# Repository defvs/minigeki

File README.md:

# M.I.N.I.G.E.K.I : a portable ONGEKI controller

A portable implementation of an ONGEKI controller, with all necessary buttons, two macros, RGB LED support, USB-C.

## Hardware setup

- Raspberry RP2040 microcontroller
- 10 hotswappable Cherry MX switches (2x Start, 2x Wall, 2x R+G+B), 2 Macro switches
- 10 RGB daisy-chained WS2812-compatible LEDs (Under every switch except Start, and two under the board)
- USB Type-C connector for both data and power. 

## Software capabilities

- HID Gamepad mode or HID Mouse/Keyboard mode
    - Switchable on boot
- Software addressable RGB via HID
- Auto-rollback to static RGB LEDs if no HID is detected
    - LED can be disabled on boot
- High polling rate
- Switch debouncing
- 8-bit slider position

## Based on / sources

- This project's code is based on SpeedyPotato's [Pico-Game-Controller](https://github.com/speedypotato/Pico-Game-Controller)
    - It also includes sources from Raspberry Pi's [pico-examples](https://github.com/raspberrypi/pico-examples)
- This project's PCB is based on Raspberry Pi's [RP2040-Minimal design](https://datasheets.raspberrypi.com/rp2040/Minimal-KiCAD.zip)

## License and Open Source licensing

minigeki is under GPLv3 in compliance with the usage of existing GPLv3 code. License information can be found in the LICENSE file.

A list of open source components and their licenses can be found in the LICENSING file.

## Extra credit and thank you

- CrazyRedMachine
- megumi_akasaka
- SpeedyPotato

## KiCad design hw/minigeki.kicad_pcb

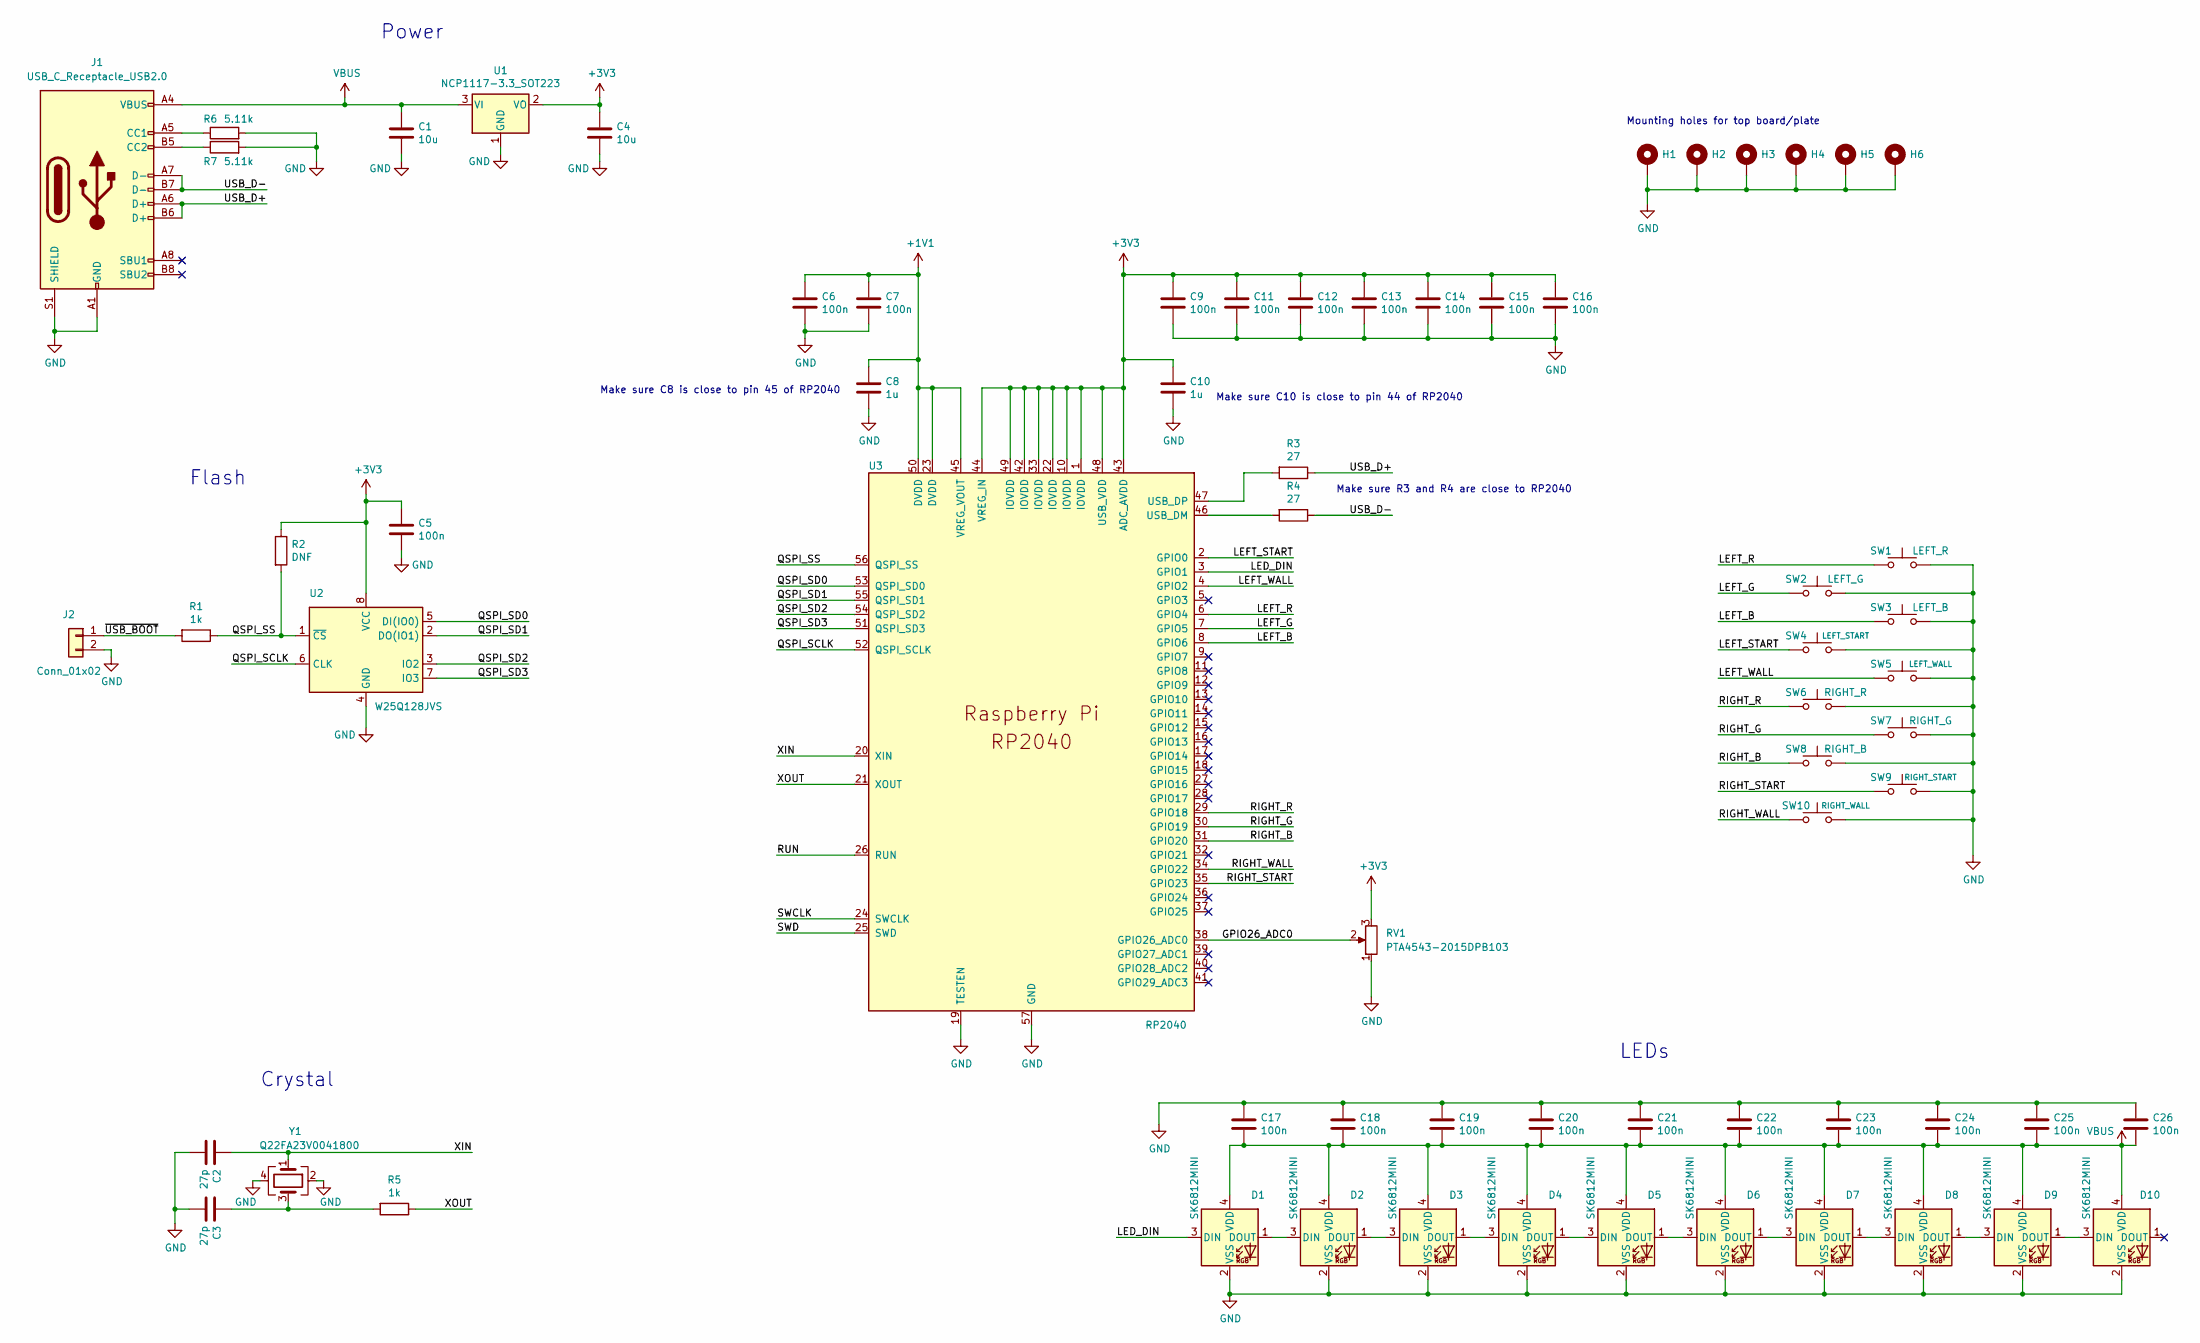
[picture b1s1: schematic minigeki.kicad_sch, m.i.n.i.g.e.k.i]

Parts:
C1, C4: 10u; C_0805_2012Metric
C2, C3: 27p; C_0402_1005Metric
C5, C6, C7, C9, C11, C12, C13, C14, C15, C16, C17, C18, C19, C20, C21, C22, C23, C24, C25, C26: 100n; C_0402_1005Metric
C8, C10: 1u; C_0402_1005Metric
D1, D2, D3, D4, D5, D6, D7, D8, D9, D10: SK6812MINI; LED_SK6812MINI_PLCC4_3.5x3.5mm_P1.75mm; MPN SK6812MINI
H1, H2, H3, H4, H5, H6: MountingHole_Pad; MountingHole_2.2mm_M2_Pad_TopOnly
J1: USB_C_Receptacle_USB2.0; USB_C_Receptacle_XKB_U262-16XN-4BVC11; MPN U262-161N-4BVC11
J2: Conn_01x02; PinHeader_1x02_P2.54mm_Vertical
R1, R5: 1k; C_0402_1005Metric
R2: DNF; C_0402_1005Metric
R3, R4: 27; C_0402_1005Metric
R6, R7: 5.11k; R_0402_1005Metric
RV1: PTA4543-2015DPB103; PTAXX43; MPN PTA4543-2015DPB103
SW1: LEFT_R; SW_Hotswap_Kailh_MX_1.00u
SW2: LEFT_G; SW_Hotswap_Kailh_MX_1.00u
SW3: LEFT_B; SW_Hotswap_Kailh_MX_1.00u
SW4: LEFT_START; SW_Hotswap_Kailh_MX_1.00u
SW5: LEFT_WALL; SW_Hotswap_Kailh_MX_2.00u
SW6: RIGHT_R; SW_Hotswap_Kailh_MX_1.00u
SW7: RIGHT_G; SW_Hotswap_Kailh_MX_1.00u
SW8: RIGHT_B; SW_Hotswap_Kailh_MX_1.00u
SW9: RIGHT_START; SW_Hotswap_Kailh_MX_1.00u
SW10: RIGHT_WALL; SW_Hotswap_Kailh_MX_2.00u
U1: NCP1117-3.3_SOT223; SOT-223-3_TabPin2; MPN NCP1117ST33T3G
U2: W25Q128JVS; SOIC-8_5.23x5.23mm_P1.27mm; MPN W25Q128JVS
U3: RP2040; RP2040-QFN-56; MPN RP2040
Y1: Q22FA23V0041800; Crystal_SMD_3225-4Pin_3.2x2.5mm; MPN Q22FA23V0041800

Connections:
+1V1: C6.1, C7.1, C8.1, U3.23 (DVDD), U3.45 (VREG_VOUT), U3.50 (DVDD)
+3V3: C4.1, C5.1, C9.1, C10.1, C11.1, C12.1, C13.1, C14.1, C15.1, C16.1, R2.1, RV1.3, U1.2 (VO), U2.8 (VCC), U3.1 (IOVDD), U3.10 (IOVDD), U3.22 (IOVDD), U3.33 (IOVDD), U3.42 (IOVDD), U3.43 (ADC_AVDD), U3.44 (VREG_IN), U3.48 (USB_VDD), U3.49 (IOVDD)
/GPIO26_ADC0: RV1.2, U3.38 (GPIO26_ADC0)
/LED_DIN: D1.3 (DIN), U3.3 (GPIO1)
/LEFT_B: SW3.1, U3.8 (GPIO6)
/LEFT_G: SW2.1, U3.7 (GPIO5)
/LEFT_R: SW1.1, U3.6 (GPIO4)
/LEFT_START: SW4.1, U3.2 (GPIO0)
/LEFT_WALL: SW5.1, U3.4 (GPIO2)
/QSPI_SCLK: U2.6 (CLK), U3.52 (QSPI_SCLK)
/QSPI_SD0: U2.5 (DI(IO0)), U3.53 (QSPI_SD0)
/QSPI_SD1: U2.2 (DO(IO1)), U3.55 (QSPI_SD1)
/QSPI_SD2: U2.3 (IO2), U3.54 (QSPI_SD2)
/QSPI_SD3: U2.7 (IO3), U3.51 (QSPI_SD3)
/QSPI_SS: R1.1, R2.2, U2.1 (~CS), U3.56 (QSPI_SS)
/RIGHT_B: SW8.1, U3.31 (GPIO20)
/RIGHT_G: SW7.1, U3.30 (GPIO19)
/RIGHT_R: SW6.1, U3.29 (GPIO18)
/RIGHT_START: SW9.1, U3.35 (GPIO23)
/RIGHT_WALL: SW10.1, U3.34 (GPIO22)
/RUN: U3.26 (RUN)
/SWCLK: U3.24 (SWCLK)
/SWD: U3.25 (SWD)
/USB_D+: J1.A6 (D+), J1.B6 (D+), R3.1
/USB_D-: J1.A7 (D-), J1.B7 (D-), R4.1
/XIN: C2.1, U3.20 (XIN), Y1.1
/XOUT: R5.1, U3.21 (XOUT)
/~USB_BOOT: J2.1, R1.2
GND: C1.2, C2.2, C3.2, C4.2, C5.2, C6.2, C7.2, C8.2, C9.2, C10.2, C11.2, C12.2, C13.2, C14.2, C15.2, C16.2, C17.1, C18.1, C19.1, C20.1, C21.1, C22.1, C23.1, C24.1, C25.1, C26.1, D1.2 (VSS), D2.2 (VSS), D3.2 (VSS), D4.2 (VSS), D5.2 (VSS), D6.2 (VSS), D7.2 (VSS), D8.2 (VSS), D9.2 (VSS), D10.2 (VSS), H1.1, H2.1, H3.1, H4.1, H5.1, H6.1, J1.A1 (GND), J1.A12 (GND), J1.B1 (GND), J1.B12 (GND), J1.S1 (SHIELD), J2.2, R6.2, R7.2, RV1.1, SW1.2, SW2.2, SW3.2, SW4.2, SW5.2, SW6.2, SW7.2, SW8.2, SW9.2, SW10.2, U1.1 (GND), U2.4 (GND), U3.19 (TESTEN), U3.57 (GND), Y1.2, Y1.4
unnamed: C3.1, R5.2, Y1.3
unnamed: D1.1 (DOUT), D2.3 (DIN)
unnamed: D2.1 (DOUT), D3.3 (DIN)
unnamed: D3.1 (DOUT), D4.3 (DIN)
unnamed: D4.1 (DOUT), D5.3 (DIN)
unnamed: D5.1 (DOUT), D6.3 (DIN)
unnamed: D6.1 (DOUT), D7.3 (DIN)
unnamed: D7.1 (DOUT), D8.3 (DIN)
unnamed: D8.1 (DOUT), D9.3 (DIN)
unnamed: D9.1 (DOUT), D10.3 (DIN)
unnamed: J1.A5 (CC1), R6.1
unnamed: J1.B5 (CC2), R7.1
unnamed: R3.2, U3.47 (USB_DP)
unnamed: R4.2, U3.46 (USB_DM)
VBUS: C1.1, C17.2, C18.2, C19.2, C20.2, C21.2, C22.2, C23.2, C24.2, C25.2, C26.2, D1.4 (VDD), D2.4 (VDD), D3.4 (VDD), D4.4 (VDD), D5.4 (VDD), D6.4 (VDD), D7.4 (VDD), D8.4 (VDD), D9.4 (VDD), D10.4 (VDD), J1.A4 (VBUS), J1.A9 (VBUS), J1.B4 (VBUS), J1.B9 (VBUS), U1.3 (VI)

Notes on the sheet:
Mounting holes for top board/plate
LEDs
Make sure C10 is close to pin 44 of RP2040
Power
Crystal
Make sure C8 is close to pin 45 of RP2040
Flash
Make sure R3 and R4 are close to RP2040

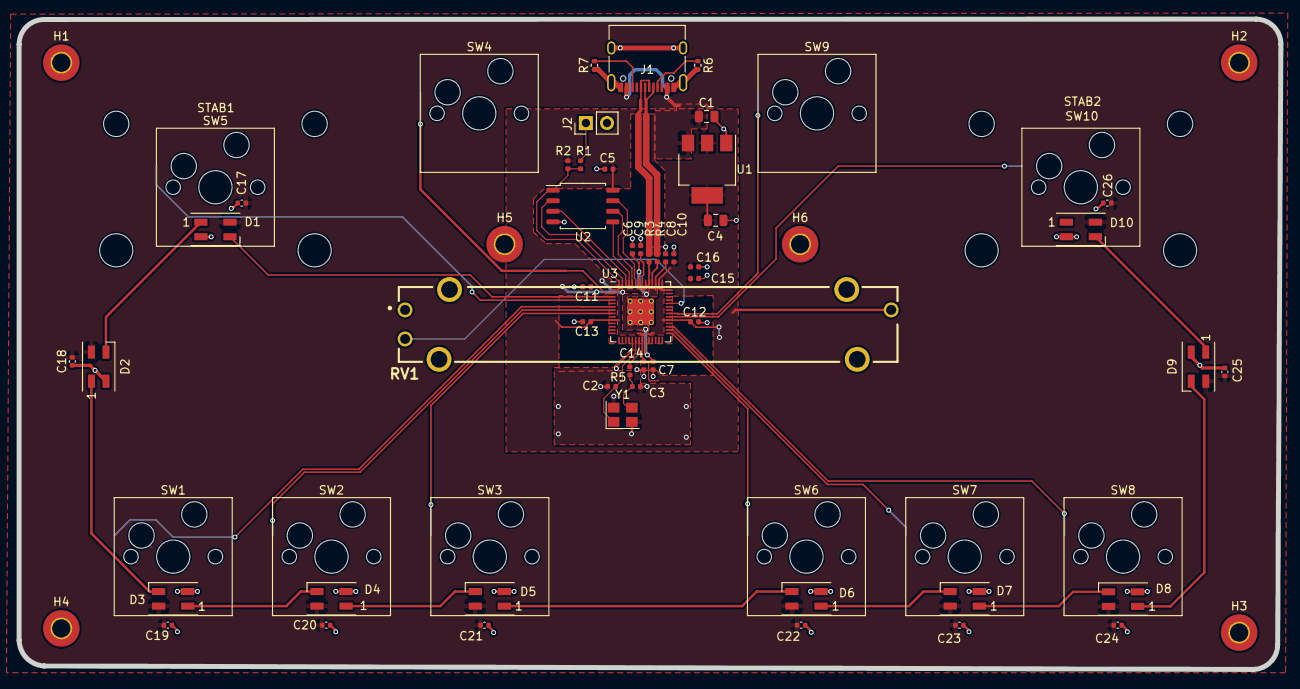
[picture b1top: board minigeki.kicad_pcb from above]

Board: 2 copper layers, 151.8 x 78.3 mm, 68 parts (0 on the bottom side), 41 nets.

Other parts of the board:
STAB1, STAB2: Stabilizer_Cherry_MX_2.00u

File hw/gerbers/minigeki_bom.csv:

"Item","Qty","Reference(s)","Value","LibPart","Footprint","Datasheet","Description","Load Capacitance","MPN","Package"
"1","2","C1, C4","10u","Device:C","Capacitor_SMD:C_0805_2012Metric","~","","","","0805"
"2","2","C2, C3","27p","Device:C","Capacitor_SMD:C_0402_1005Metric","~","","","","0402"
"3","20","C5, C6, C7, C9, C11, C12, C13, C14, C15, C16, C17, C18, C19, C20, C21, C22, C23, C24, C25, C26","100n","Device:C","Capacitor_SMD:C_0402_1005Metric","~","","","","0402"
"4","2","C8, C10","1u","Device:C","Capacitor_SMD:C_0402_1005Metric","~","","","","0402"
"5","10","D1, D2, D3, D4, D5, D6, D7, D8, D9, D10","SK6812MINI","LED:SK6812MINI","LED_SMD:LED_SK6812MINI_PLCC4_3.5x3.5mm_P1.75mm","https://cdn-shop.adafruit.com/product-files/2686/SK6812MINI_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","SK6812MINI","","SK6812MINI","PLCC4_3.5x3.5mm_P1.75mm"
"6","1","J1","USB_C_Receptacle_USB2.0","Connector:USB_C_Receptacle_USB2.0","Connector_USB:USB_C_Receptacle_XKB_U262-16XN-4BVC11","https://www.usb.org/sites/default/files/documents/usb_type-c.zip","U262-161N-4BVC11","","U262-161N-4BVC11","U262-161N-4BVC11"
"8","2","R1, R5","1k","Device:R","Capacitor_SMD:C_0402_1005Metric","~","","","","0402"
"9","1","R2","DNF","Device:R","Capacitor_SMD:C_0402_1005Metric","~","","","","0402"
"10","2","R3, R4","27","Device:R","Capacitor_SMD:C_0402_1005Metric","~","","","","0402"
"11","2","R6, R7","5.11k","Device:R","Resistor_SMD:R_0402_1005Metric","~","","","","0402"
"12","1","RV1","PTA4543-2015DPB103","Device:R_Potentiometer","PTAXX33:PTAXX43","~","PTA4543-2015DPB103","","PTA4543-2015DPB103",""
"23","1","U1","NCP1117-3.3_SOT223","Regulator_Linear:NCP1117-3.3_SOT223","Package_TO_SOT_SMD:SOT-223-3_TabPin2","http://www.onsemi.com/pub_link/Collateral/NCP1117-D.PDF","NCP1117ST33T3G","","NCP1117ST33T3G","SOT223-3"
"24","1","U2","W25Q128JVS","Memory_Flash:W25Q128JVS","Package_SO:SOIC-8_5.23x5.23mm_P1.27mm","http://www.winbond.com/resource-files/w25q128jv_dtr%20revc%2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","W25Q128JVS","","W25Q128JVS","SOIC-8_5.23x5.23mm_P1.27mm"
"25","1","U3","RP2040","MCU_RaspberryPi_RP2040:RP2040","RP2040_minimal:RP2040-QFN-56","","RP2040","","RP2040","QFN-56"
"26","1","Y1","Q22FA23V0041800","Device:Crystal_GND24","Crystal:Crystal_SMD_3225-4Pin_3.2x2.5mm","https://datasheet.lcsc.com/lcsc/1811051112_Seiko-Epson-Q22FA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","Q22FA23V0041800","18p","Q22FA23V0041800","MD_3225-4Pin_3.2x2.5mm"

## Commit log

2022-05-18 Init platformio project
2022-05-18 Add library HID as submodule
2022-05-18 Create program files
2022-05-18 Convert to CLion project
2022-05-18 Buttons to HID Gamepad implementation
2022-05-19 Add v1 hardware files
2022-05-19 Update code style (use tabs)
2022-05-20 Add v2 hardware files
2022-05-20 Add v2 software files
2022-05-24 hw: Add linear potentiometer
2022-05-24 hw: rename kicad project
2022-05-24 hw: finish main routing
2022-05-24 hw: final routing pass
2022-05-24 hw: update schematic to reflect PCB changes
2022-05-24 sw: adapt codebase for our controller
2022-05-25 sw: fix LED code
2022-05-25 Cleanup and add licensing information
2022-05-25 Create minigeki graphics
2022-05-25 Fix logo
2022-05-25 Add white background to logo png
2022-05-25 Add logo to README
2022-05-28 hw: add mounting holes
2022-05-28 hw: v2 gerbers export
2022-05-28 hw: fix GND copper area not filling everything
2022-06-08 hw: add mounting holes, flip components to top of the board
2022-06-09 hw: final PCB for v3.0
2022-06-09 hw: export gerber
2022-06-12 Clean up BOM
2022-08-10 hw: final prototype export
